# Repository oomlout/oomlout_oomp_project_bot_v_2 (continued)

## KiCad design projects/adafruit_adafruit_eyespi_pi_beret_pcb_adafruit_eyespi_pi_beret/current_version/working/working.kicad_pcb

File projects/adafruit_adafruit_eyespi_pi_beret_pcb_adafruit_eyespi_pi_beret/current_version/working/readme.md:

# adafruit_eyespi_pi_beret_pcb
 
## summary 
* id: adafruit_adafruit_eyespi_pi_beret_pcb_adafruit_eyespi_pi_beret
* user: adafruit
* name: adafruit_eyespi_pi_beret_pcb
* board: adafruit_eyespi_pi_beret
* repo: https://github.com/adafruit/Adafruit-EYESPI-Pi-Beret-PCB

* src_file_repo_sch: 
* src_file_repo_sch_link: https://github.com/adafruit/Adafruit-EYESPI-Pi-Beret-PCB/tree/main/
* full details link: https://github.com/oomlout/oomlout_oomp_project_bot_v_2/tree/main/projects/adafruit_adafruit_eyespi_pi_beret_pcb_adafruit_eyespi_pi_beret/current_version/working  

## schematic  
  
[schematic (pdf)](working_schematic.pdf) 

## pcb  

[board (pdf)](working.pdf)  

## working_bom
| Id | Designator | Footprint | Quantity | Designation | Supplier and ref |  | None | 
| --- | --- | --- | --- | --- | --- | --- | --- | 
| 1 | U$9 | PCBFEAT-REV-040 | 1 |  |  |  | [''] | 
| 2 | R4,R1,R2 | RESPACK_4X0603 | 3 | 10K Pack |  |  | [''] | 
| 3 | @HOLE0,@HOLE1 |  | 2 |  |  |  | [''] | 
| 4 | PLABEL0 | PLABEL0 | 1 |  |  |  | [''] | 
| 5 | X1 | EYE_SPI_DISPLAY_BOTCONTACT | 1 | EYE_SPI_DISPLAY_FLIP |  |  | [''] | 
| 6 | CONN2 | JST_SH4 | 1 | STEMMA_I2C_QT |  |  | [''] | 
| 7 | FID4,FID1 | FIDUCIAL_1MM | 2 | FIDUCIAL_1MM |  |  | [''] | 
| 8 | SW1,SW2 | TACTILE_3X6MM | 2 | SWITCH_SPST_NOMNT_3X6 |  |  | [''] | 
| 9 | PLABEL3 | PLABEL3 | 1 |  |  |  | [''] | 
| 10 | PLABEL2 | PLABEL2 | 1 |  |  |  | [''] | 
| 11 | PLABEL1 | PLABEL1 | 1 |  |  |  | [''] | 
| 12 | PLABEL4 | PLABEL4 | 1 |  |  |  | [''] | 
| 13 | SW3 | EG1390 | 1 | SLIDE |  |  | [''] | 
| 14 | SJ1 | SOLDERJUMPER_CLOSEDWIRE | 1 |  |  |  | [''] | 
| 15 | RPI2 | RASPI_2X20_THMSMT | 1 | RASPBERRYPI_BPLUS_2X20_THMSMT |  |  | [''] | 
| 16 | U$24 | ADAFRUIT_3.5MM | 1 |  |  |  | [''] | 
| 17 | C1,C21 | 0805-NO | 2 | 10uF |  |  | [''] | 
| 18 | U$30 | STEMMAQT | 1 |  |  |  | [''] | 
| 19 | PLABEL6 | PLABEL6 | 1 |  |  |  | [''] | 
| 20 | PLABEL5 | PLABEL5 | 1 |  |  |  | [''] | 

## bom_schematic
| Ref | Qnty | Value | Cmp name | Footprint | Description | Vendor | DNP | 
| --- | --- | --- | --- | --- | --- | --- | --- | 
| C1, C21 | 2 | 10uF | CAP_CERAMIC0805-NOOUTLINE | working:0805-NO |  |  |  | 
| CONN2 | 1 | STEMMA_I2C_QT | STEMMA_I2C_QT | working:JST_SH4 |  |  |  | 
| FID1, FID4 | 2 | FIDUCIAL_1MM | FIDUCIAL_1MM | working:FIDUCIAL_1MM |  |  |  | 
| R1, R2, R4 | 3 | 10K Pack | RESISTOR_4PACK | working:RESPACK_4X0603 |  |  |  | 
| RPI2 | 1 | RASPBERRYPI_BPLUS_2X20_THMSMT | RASPBERRYPI_BPLUS_2X20_THMSMT | working:RASPI_2X20_THMSMT |  |  |  | 
| SJ1 | 1 | SOLDERJUMPERCLOSED | SOLDERJUMPERCLOSED | working:SOLDERJUMPER_CLOSEDWIRE |  |  |  | 
| SW1, SW2 | 2 | SWITCH_SPST_NOMNT_3X6 | SWITCH_SPST_NOMNT_3X6 | working:TACTILE_3X6MM |  |  |  | 
| SW3 | 1 | SLIDE | SWITCH_DPDTEG1390 | working:EG1390 |  |  |  | 
| X1 | 1 | EYE_SPI_DISPLAY_FLIP | EYE_SPI_DISPLAY_FLIP | working:EYE_SPI_DISPLAY_BOTCONTACT |  |  |  |

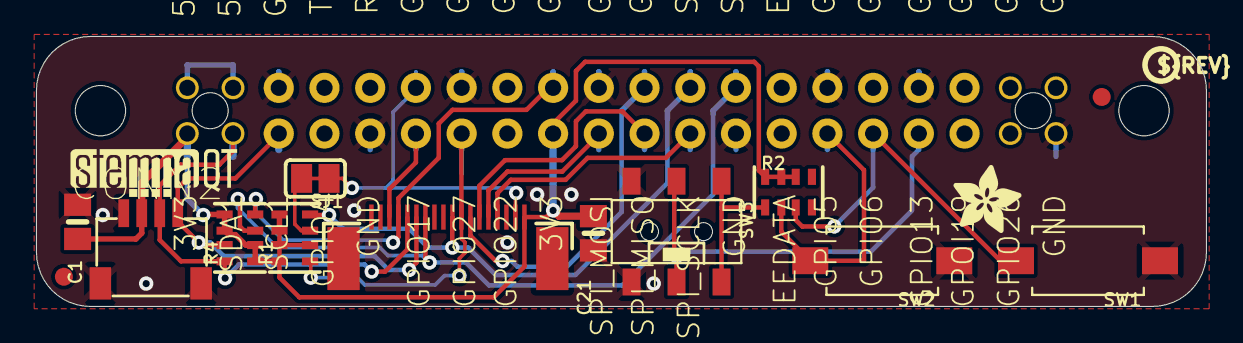
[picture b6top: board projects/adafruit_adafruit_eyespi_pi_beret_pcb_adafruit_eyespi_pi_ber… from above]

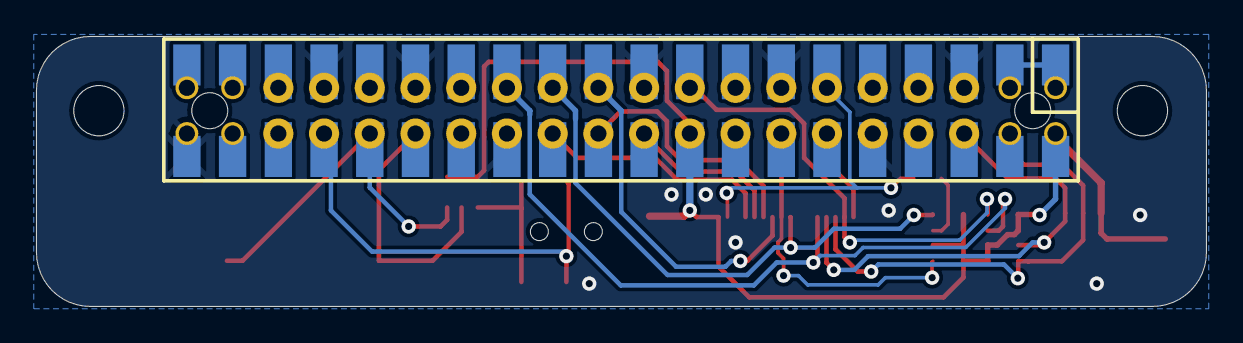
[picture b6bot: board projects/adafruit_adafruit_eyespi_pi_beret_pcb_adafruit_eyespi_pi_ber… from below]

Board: 2 copper layers, 65.0 x 15.0 mm, 26 parts (2 on the bottom side), 20 nets.

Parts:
@HOLE0, @HOLE1: (no value)
C1, C21: 10uF; 0805-NO
CONN2: STEMMA_I2C_QT; JST_SH4
FID1, FID4: FIDUCIAL_1MM
PLABEL0: PLABEL0
PLABEL1: PLABEL1
PLABEL2: PLABEL2
PLABEL3: PLABEL3
PLABEL4: PLABEL4
PLABEL5: PLABEL5
PLABEL6: PLABEL6
R1, R2, R4: 10K Pack; RESPACK_4X0603
RPI2: RASPBERRYPI_BPLUS_2X20_THMSMT; RASPI_2X20_THMSMT
SJ1: SOLDERJUMPER_CLOSEDWIRE
SW1, SW2: SWITCH_SPST_NOMNT_3X6; TACTILE_3X6MM
SW3: SLIDE; EG1390
U$9: PCBFEAT-REV-040
U$24: ADAFRUIT_3.5MM
U$30: STEMMAQT
X1: EYE_SPI_DISPLAY_FLIP; EYE_SPI_DISPLAY_BOTCONTACT

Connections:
3.3V: C1.2, C21.1, CONN2.2, R1.2, R1.5, R1.6, R1.7, R1.8, R2.6, R2.7, R2.8, R4.1, R4.2, R4.5, R4.6, RPI2.1, RPI2.17, RPI2.S1, RPI2.S17, X1.1
5.0V: RPI2.2, RPI2.4, RPI2.S2, RPI2.S4
BACKLITE: RPI2.12, RPI2.S12, SJ1.1, X1.2
BUSY: RPI2.11, RPI2.S11, X1.16
GND: C1.1, C21.2, CONN2.1, CONN2.MT1, CONN2.MT2, RPI2.6, RPI2.9, RPI2.14, RPI2.20, RPI2.25, RPI2.30, RPI2.34, RPI2.39, RPI2.S6, RPI2.S9, RPI2.S14, RPI2.S20, RPI2.S25, RPI2.S30, RPI2.S34, RPI2.S39, SW1.P$1, SW2.P$1, SW3.S1, SW3.S2, X1.3, X1.SUPPORT1, X1.SUPPORT2
GPIO5: R2.2, RPI2.29, RPI2.S29, SW2.P$2
GPIO6: R2.3, RPI2.31, RPI2.S31, SW1.P$2
GPIO13: RPI2.33, RPI2.S33, SW3.P1, SW3.P2
IRQ: R4.4, RPI2.18, RPI2.S18, X1.15
MISO: RPI2.21, RPI2.S21, X1.6
MOSI: RPI2.19, RPI2.S19, X1.5
unnamed: R1.3, SJ1.2
unnamed: R2.1, SW3.O1, SW3.O2
RESET: R1.1, RPI2.13, RPI2.S13, X1.8
SCL: CONN2.4, R4.7, RPI2.5, RPI2.S5, X1.13
SCLK: RPI2.23, RPI2.S23, X1.4
SDA: CONN2.3, R4.8, RPI2.3, RPI2.S3, X1.14
TFT_CS: R1.4, RPI2.24, RPI2.S24, X1.9
TFT_DC: RPI2.22, RPI2.S22, X1.7
TOUCH_CS: R4.3, RPI2.26, RPI2.S26, X1.12

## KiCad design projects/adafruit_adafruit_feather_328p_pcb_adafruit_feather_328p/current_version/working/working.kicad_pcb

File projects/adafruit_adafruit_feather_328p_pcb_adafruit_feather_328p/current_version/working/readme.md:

# adafruit_feather_328p_pcb
 
## summary 
* id: adafruit_adafruit_feather_328p_pcb_adafruit_feather_328p
* user: adafruit
* name: adafruit_feather_328p_pcb
* board: adafruit_feather_328p
* repo: https://github.com/adafruit/Adafruit-Feather-328P-PCB

* src_file_repo_sch: 
* src_file_repo_sch_link: https://github.com/adafruit/Adafruit-Feather-328P-PCB/tree/master/
* full details link: https://github.com/oomlout/oomlout_oomp_project_bot_v_2/tree/main/projects/adafruit_adafruit_feather_328p_pcb_adafruit_feather_328p/current_version/working  

## schematic  
  
[schematic (pdf)](working_schematic.pdf) 

## pcb  

[board (pdf)](working.pdf)  

## working_bom
| Id | Designator | Footprint | Quantity | Designation | Supplier and ref |  | None | 
| --- | --- | --- | --- | --- | --- | --- | --- | 
| 1 | D3 | CHIPLED_0805_NOOUTLINE | 1 | RED |  |  | [''] | 
| 2 | U$32,U$31 | MOUNTINGHOLE_2.5_PLATED | 2 | MOUNTINGHOLE2.5 |  |  | [''] | 
| 3 | U2 | SOT23-5 | 1 | AP2112-3.3 |  |  | [''] | 
| 4 | Y2 | RESONATOR | 1 | CSTNE8M00xx 8MHZ |  |  | [''] | 
| 5 | C11,C8 | 0603-NO | 2 | 1uF |  |  | [''] | 
| 6 | U3 | SOT23-5 | 1 | MCP73831T-2ACI/OT |  |  | [''] | 
| 7 | C5,C9,C10,C4 | 0603-NO | 4 | 0.1uF |  |  | [''] | 
| 8 | U$34,U$35 | FIDUCIAL_1MM | 2 | FIDUCIAL_1MM |  |  | [''] | 
| 9 | D5,D1 | CHIPLED_0805_NOOUTLINE | 2 | YELLOW |  |  | [''] | 
| 10 | R10,R6,R7,R2 | 0603-NO | 4 | 1K |  |  | [''] | 
| 11 | U$15,U$44 | ADAFRUIT_3.5MM | 2 |  |  |  | [''] | 
| 12 | @HOLE0,@HOLE1 |  | 2 |  |  |  | [''] | 
| 13 | R5 | RESPACK_4X0603 | 1 | 100K |  |  | [''] | 
| 14 | SW2 | BTN_KMR2_4.6X2.8 | 1 | KMR2 |  |  | [''] | 
| 15 | R4,R8 | 0603-NO | 2 | 10K |  |  | [''] | 
| 16 | D4 | SOD-123 | 1 | MBR120 |  |  | [''] | 
| 17 | IC2 | MLF32-TH | 1 | ATMEGA328P |  |  | [''] | 
| 18 | X1 | JSTPH2 | 1 | JSTPH |  |  | [''] | 
| 19 | C3,C6 | 0805-NO | 2 | 10ÂµF |  |  | [''] | 
| 20 | C2,C1 | 0805-NO | 2 | 10uF |  |  | [''] | 
| 21 | CHG0 | CHIPLED_0805_NOOUTLINE | 1 | ORANGE |  |  | [''] | 
| 22 | C7 | _0805MP | 1 | 10uF |  |  | [''] | 
| 23 | R1 | _0603MP | 1 | 1K |  |  | [''] | 
| 24 | IC1 | QFN24_4MM_SMSC | 1 | CP2104 |  |  | [''] | 
| 25 | Q3 | SOT23-R | 1 | DMG341 |  |  | [''] | 
| 26 | X4 | 4UCONN_20329_V2 | 1 | 20329 |  |  | [''] | 
| 27 | JP1 | 1X16_ROUND | 1 |  |  |  | [''] | 
| 28 | JP3 | 1X12_ROUND | 1 |  |  |  | [''] | 
| 29 | U$9 | FEATHERLOGO | 1 |  |  |  | [''] | 
| 30 | U$13 | PCBFEAT-REV-040 | 1 |  |  |  | [''] | 

## bom_schematic
| Ref | Qnty | Value | Cmp name | Footprint | Description | Vendor | DNP | 
| --- | --- | --- | --- | --- | --- | --- | --- | 
| C1, C2 | 2 | 10uF | CAP_CERAMIC0805-NOOUTLINE | working:0805-NO |  |  |  | 
| C3, C6 | 2 | 10ÂµF | CAP_CERAMIC0805-NOOUTLINE | working:0805-NO |  |  |  | 
| C4, C5, C9, C10 | 4 | 0.1uF | CAP_CERAMIC0603_NO | working:0603-NO |  |  |  | 
| C7 | 1 | 10uF | CAP_CERAMIC_0805MP | working:_0805MP |  |  |  | 
| C8, C11 | 2 | 1uF | CAP_CERAMIC0603_NO | working:0603-NO |  |  |  | 
| CHG0 | 1 | ORANGE | LED0805_NOOUTLINE | working:CHIPLED_0805_NOOUTLINE |  |  |  | 
| D1, D5 | 2 | YELLOW | LED0805_NOOUTLINE | working:CHIPLED_0805_NOOUTLINE |  |  |  | 
| D3 | 1 | RED | LED0805_NOOUTLINE | working:CHIPLED_0805_NOOUTLINE |  |  |  | 
| D4 | 1 | MBR120 | DIODE-SCHOTTKYSOD-123 | working:SOD-123 |  |  |  | 
| IC1 | 1 | CP2104 | CP2104 | working:QFN24_4MM_SMSC |  |  |  | 
| IC2 | 1 | MEGA8-MI | MEGA8-MI | working:MLF32-TH |  |  |  | 
| JP1 | 1 | HEADER-1X16ROUND | HEADER-1X16ROUND | working:1X16_ROUND |  |  |  | 
| JP3 | 1 | HEADER-1X12 | HEADER-1X12 | working:1X12_ROUND |  |  |  | 
| Q3 | 1 | DMG341 | MOSFET-P | working:SOT23-R |  |  |  | 
| R1 | 1 | 1K | RESISTOR_0603MP | working:_0603MP |  |  |  | 
| R2, R6, R7, R10 | 4 | 1K | RESISTOR_0603_NOOUT | working:0603-NO |  |  |  | 
| R4, R8 | 2 | 10K | RESISTOR_0603_NOOUT | working:0603-NO |  |  |  | 
| R5 | 1 | 100K | RESISTOR_4PACK | working:RESPACK_4X0603 |  |  |  | 
| SW2 | 1 | KMR2 | SWITCH_TACT_SMT4.6X2.8 | working:BTN_KMR2_4.6X2.8 |  |  |  | 
| U2 | 1 | AP2112-3.3 | VREG_SOT23-5 | working:SOT23-5 |  |  |  | 
| U3 | 1 | MCP73831T-2ACI/OT | MCP73831/2 | working:SOT23-5 |  |  |  | 
| U$31, U$32 | 2 | MOUNTINGHOLE2.5 | MOUNTINGHOLE2.5 | working:MOUNTINGHOLE_2.5_PLATED |  |  |  | 
| U$34, U$35 | 2 | FIDUCIAL_1MM | FIDUCIAL_1MM | working:FIDUCIAL_1MM |  |  |  | 
| X1 | 1 | JSTPH | CON_JST_PH_2PIN | working:JSTPH2 |  |  |  | 
| X4 | 1 | 20329 | USB_MICRO_20329_V2 | working:4UCONN_20329_V2 |  |  |  | 
| Y2 | 1 | RESONATORMU | RESONATORMU | working:RESONATOR |  |  |  | 

## mounting_holes
| x | y | package | value | ref | size | 
| --- | --- | --- | --- | --- | --- | 
| 0.0 | 17.78 | MOUNTINGHOLE_2.5_PLATED | MOUNTINGHOLE2.5 | U$31 | m3 | 
| 0.0 | 0.0 | MOUNTINGHOLE_2.5_PLATED | MOUNTINGHOLE2.5 | U$32 | m3 |

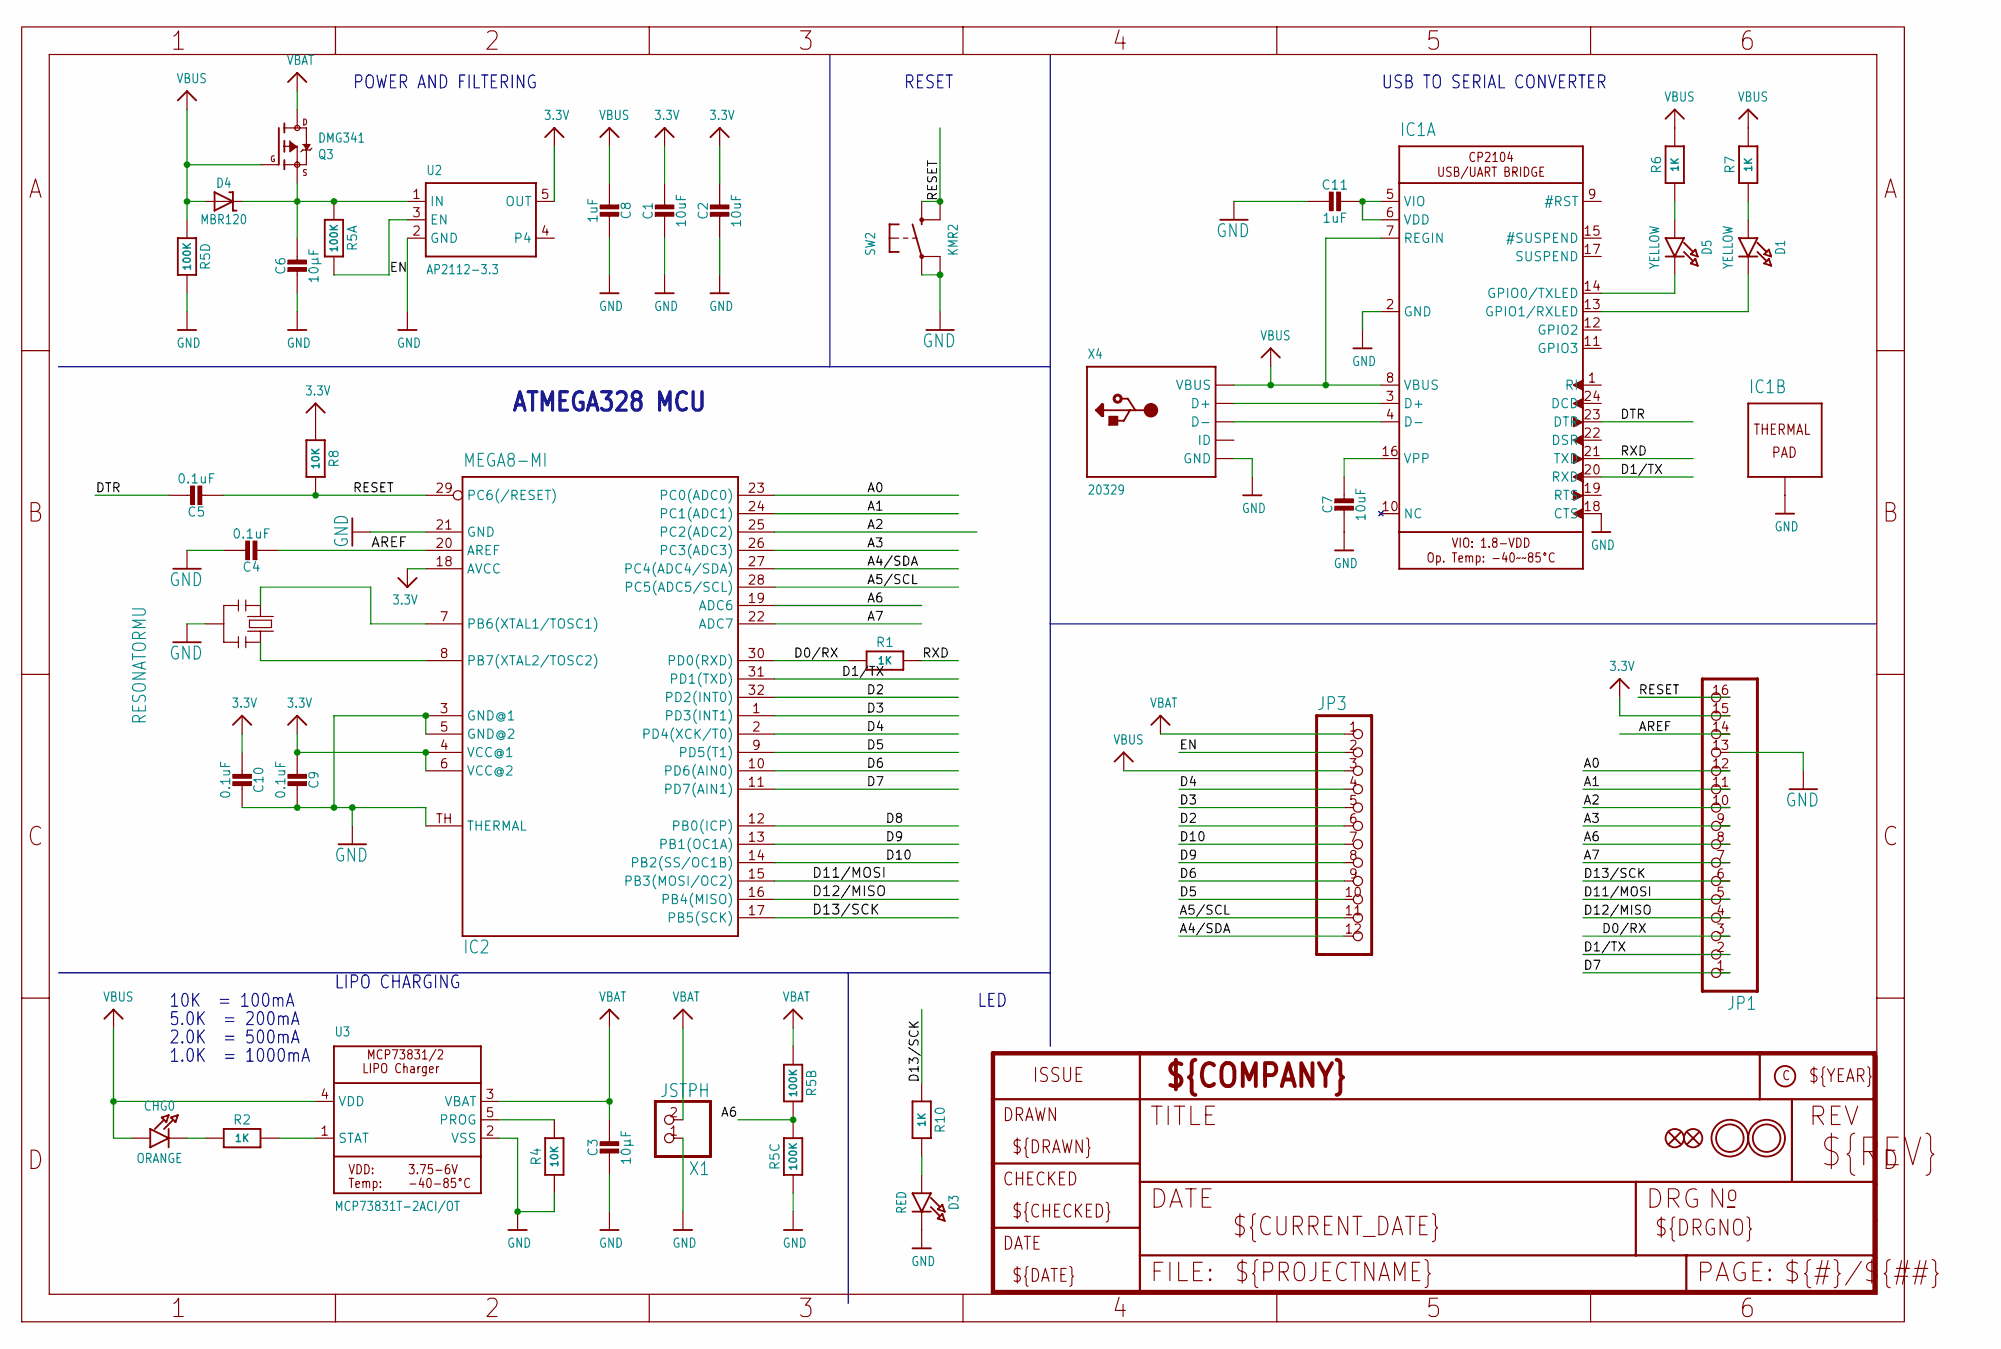
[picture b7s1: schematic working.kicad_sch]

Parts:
C1, C2: 10uF; 0805-NO
C3, C6: 10µF; 0805-NO
C4, C5, C9, C10: 0.1uF; 0603-NO
C7: 10uF; _0805MP
C8, C11: 1uF; 0603-NO
CHG0: ORANGE; CHIPLED_0805_NOOUTLINE
D1, D5: YELLOW; CHIPLED_0805_NOOUTLINE
D3: RED; CHIPLED_0805_NOOUTLINE
D4: MBR120; SOD-123
IC1: CP2104; QFN24_4MM_SMSC
IC2: MEGA8-MI; MLF32-TH
JP1: HEADER-1X16ROUND; 1X16_ROUND
JP3: HEADER-1X12; 1X12_ROUND
Q3: DMG341; SOT23-R
R1: 1K; _0603MP
R2, R6, R7, R10: 1K; 0603-NO
R4, R8: 10K; 0603-NO
R5: 100K; RESPACK_4X0603
SW2: KMR2; BTN_KMR2_4.6X2.8
U2: AP2112-3.3; SOT23-5
U3: MCP73831T-2ACI/OT; SOT23-5
U$31, U$32: MOUNTINGHOLE2.5; MOUNTINGHOLE_2.5_PLATED
U$34, U$35: FIDUCIAL_1MM
X1: JSTPH; JSTPH2
X4: 20329; 4UCONN_20329_V2
Y2: RESONATORMU; RESONATOR

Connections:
3.3V: C1.1, C2.1, C9.2, C10.2, IC2.4 (VCC@1), IC2.6 (VCC@2), IC2.18 (AVCC), JP1.15, R8.2, U2.5 (OUT)
A0: IC2.23 (PC0(ADC0)), JP1.12
A1: IC2.24 (PC1(ADC1)), JP1.11
A2: IC2.25 (PC2(ADC2)), JP1.10
A3: IC2.26 (PC3(ADC3)), JP1.9
A4/SDA: IC2.27 (PC4(ADC4/SDA)), JP3.12
A5/SCL: IC2.28 (PC5(ADC5/SCL)), JP3.11
A6: IC2.19 (ADC6), JP1.8, R5.6 (2), R5.7 (2)
A7: IC2.22 (ADC7), JP1.7
AREF: C4.2, IC2.20 (AREF), JP1.14
D0/RX: IC2.30 (PD0(RXD)), JP1.3, R1.1
D1/TX: IC1.20 (RXD), IC2.31 (PD1(TXD)), JP1.2
D2: IC2.32 (PD2(INT0)), JP3.6
D3: IC2.1 (PD3(INT1)), JP3.5
D4: IC2.2 (PD4(XCK/T0)), JP3.4
D5: IC2.9 (PD5(T1)), JP3.10
D6: IC2.10 (PD6(AIN0)), JP3.9
D7: IC2.11 (PD7(AIN1)), JP1.1
D8: IC2.12 (PB0(ICP))
D9: IC2.13 (PB1(OC1A)), JP3.8
D10: IC2.14 (PB2(SS/OC1B)), JP3.7
D11/MOSI: IC2.15 (PB3(MOSI/OC2)), JP1.5
D12/MISO: IC2.16 (PB4(MISO)), JP1.4
D13/SCK: IC2.17 (PB5(SCK)), JP1.6, R10.1
DTR: C5.1, IC1.23 (DTR)
EN: JP3.2, R5.8 (2), U2.3 (EN)
GND: C1.2, C2.2, C3.2, C4.1, C6.2, C7.2, C8.1, C9.1, C10.1, C11.2, D3.C, IC1.2 (GND), IC1.18 (CTS), IC1.THERM (TP), IC2.3 (GND@1), IC2.5 (GND@2), IC2.21 (GND), IC2.TH (THERMAL), JP1.13, R4.1, R5.3 (1), R5.5 (2), SW2.A, SW2.A' (P1), U2.2 (GND), U3.2 (VSS), X1.1, X4.BASE@1 (GND), X4.BASE@2 (GND), X4.GND, X4.SPRT@1 (GND), X4.SPRT@2 (GND), X4.SPRT@3 (GND), X4.SPRT@4 (GND), Y2.2
unnamed: CHG0.C, R2.1
unnamed: IC1.3 (D+), X4.D+
unnamed: R2.2, U3.1 (STAT)
unnamed: R4.2, U3.5 (PROG)
unnamed: D3.A, R10.2
unnamed: IC1.4 (D-), X4.D-
unnamed: C6.1, D4.C, Q3.2 (S), R5.1, U2.1 (IN)
unnamed: D1.A, R7.1
unnamed: D5.A, R6.1
unnamed: C11.1, IC1.5 (VIO), IC1.6 (VDD)
unnamed: C7.1, IC1.16 (VPP)
RESET: C5.2, IC2.29 (PC6(/RESET)), JP1.16, R8.1, SW2.B (S), SW2.B' (S1)
RXD: IC1.21 (TXD), R1.2
RXLED: D1.C, IC1.13 (GPIO1/RXLED)
TXLED: D5.C, IC1.14 (GPIO0/TXLED)
VBAT: C3.1, JP3.1, Q3.3 (D), R5.2 (1), U3.3 (VBAT), X1.2
VBUS: C8.2, CHG0.A, D4.A, IC1.7 (REGIN), IC1.8 (VBUS), JP3.3, Q3.1 (G), R5.4 (1), R6.2, R7.2, U3.4 (VDD), X4.VBUS
XTAL1: IC2.8 (PB7(XTAL2/TOSC2)), Y2.3
XTAL2: IC2.7 (PB6(XTAL1/TOSC1)), Y2.1

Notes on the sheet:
10K = 100mA
5.0K = 200mA
2.0K = 500mA
LED
USB TO SERIAL CONVERTER
1.0K = 1000mA
RESET
LIPO CHARGING
ATMEGA328 MCU
POWER AND FILTERING

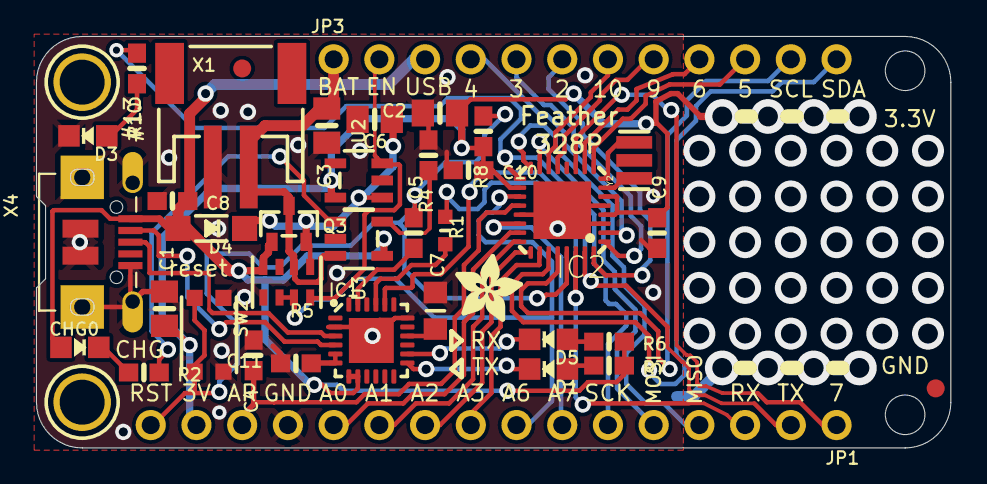
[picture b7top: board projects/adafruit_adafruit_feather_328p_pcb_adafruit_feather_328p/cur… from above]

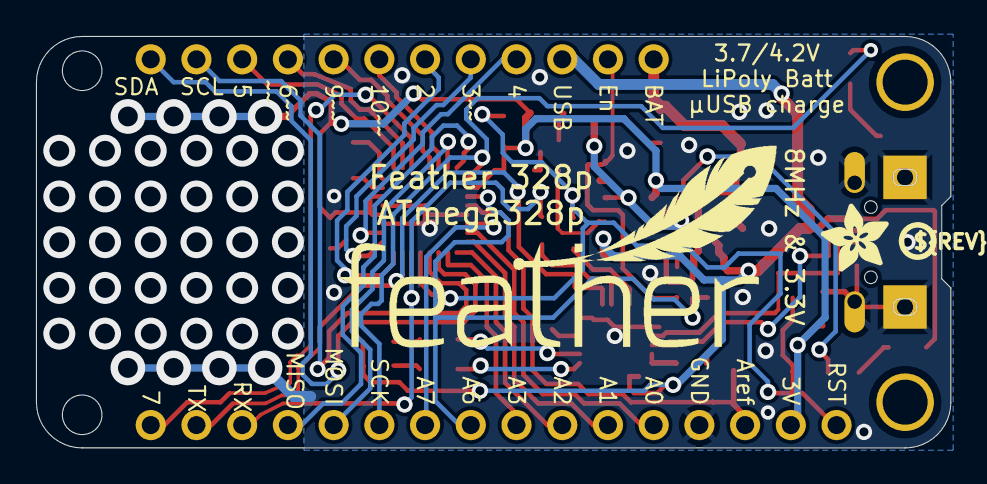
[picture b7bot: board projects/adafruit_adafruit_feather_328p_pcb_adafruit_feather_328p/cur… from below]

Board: 2 copper layers, 50.8 x 22.9 mm, 45 parts (3 on the bottom side), 45 nets.

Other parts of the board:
@HOLE0, @HOLE1: (no value)
U$9: FEATHERLOGO
U$13: PCBFEAT-REV-040
U$15, U$44: ADAFRUIT_3.5MM
